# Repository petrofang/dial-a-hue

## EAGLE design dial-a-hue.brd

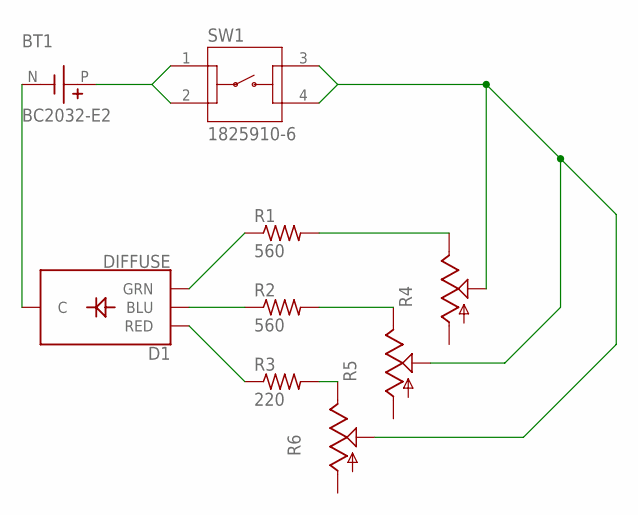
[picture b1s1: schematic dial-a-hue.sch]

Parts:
BT1: BC2032-E2; MPD_BC2032-E2
D1: DIFFUSE; LED-RGB-THRU
R1, R2: 560; 0207/10
R3: 220; 0207/10
R4, R5, R6: TRIM_US-LI10; LI10
SW1: 1825910-6; SW_1825910-6-4

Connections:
unnamed: D1.1 (RED), R3.1
unnamed: D1.4 (BLU), R2.1
unnamed: D1.3 (GRN), R1.1
unnamed: R1.2, R4.E
unnamed: R2.2, R5.E
unnamed: R3.2, R6.E
unnamed: BT1.N, D1.2 (C)
unnamed: BT1.P, SW1.1, SW1.2
unnamed: R4.S, R5.S, R6.S, SW1.3, SW1.4

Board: 2 copper layers, 9 parts (0 on the bottom side), 9 nets, no tracks yet.

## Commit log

2019-03-04 Create dial-a-hue.pdf
    dial-a-hue.pdf is a PDF exported from eagle by printing the schematic (.sch) to (.pdf).
2019-03-04 Create dial-a-hue.prototype.jpg
    A photo I took of the prototype I made from the schematic.

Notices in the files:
parts and their libraries:
gc rgb-LED: Licensing: Creative Commons ShareAlike 4.0 International - https://creativecommons.org/licenses/by-sa/4.0
